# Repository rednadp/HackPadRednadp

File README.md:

# HackPadRednadp
I have tried to create a pad similar to the stremdeck, or at least that was the idea. I have never made something similar and I have found some difficulties along the way. If you want to mount yourself the Pad you will need the materials listed bellow and the 3d-printed case.
# Final build

# Journal 
The desing is not journaled, only the building, sorry :)
# 2/7/2026 - Mounting the pcb day 1  

_Time spent: 2.0h_  

Hello, today I have been trying to figure out how to solder the components to the PCB. After watching some YouTube tutorials, I have "learned" how to solder, but when I tried to put it into practice, I encountered some problems. The first one was figuring out the positions of the components. Once that was solved, I started soldering the LED, but I had some difficulties because the pins were connecting to each other. Finally, I successfully managed to fix that, but with all those problems, I only had time to connect the LED and the diodes. I spent around 2 hours. I will continue another day. Again, sorry for my English it is not my native language :)

# 2/10/2026 10 PM - Mounting the pcb day 2  

_Time spent: 3.0h_  

Hello, today I have finished mounting all the parts to the pcb. I have found some difficulties in aligning the screen with the top plate perfectly as I have to leave a space between them because if not, the screen is too low to be seen with the cover putted.

Another difficulty that I have encountered has been inserting the inserts into the cover. I have never made it and I have made the error of not watching any tutorial, so I have done horribly bad and I will need to reprint the case and try another form of gathering the top and the bottom. The screws don't enter into the hole as it is deformed.

I also realize the necessity of modeling some stuff to turn the potentiometer better.

# 2/10/2026 11 PM - Making Rotary encoder more beautiful  

_Time spent: 0.5h_  

Hello again. I have designed stuff to put in the rotary encoder to make it more beautiful. Sadly for me I have adjusted the tolerances badly and I have to redo it again setting a compensation of -0,4mm. And, again, I have made bad adjustments so I finall decided to modify the design to make it properly.

Design:
.png)

1st attempt:

Other attempts:

# 2/17/2026 - Trying to configure the  firmware  

_Time spent: 4.0h_  

Hello, today I have suffered trying to configure the firmware. I have installed KMK into the Xiao and put all the libraries on their site. I have found some difficulties to see the errors (I have tried to use arduino IDE but after a nice talk with Gemini I have given up and I have donwloaded a program called Mu editor). I have copied the code that I did and I have realised the first problem, the pins. They were different from the diagram, (or thats what I think after intensive research on the internet and with Gemini). Finally, I have gotten the pin layout (d1, d2, etc). Then I had changed the pinout only to realise that the last row of keys was not working. Fixing that has been a terrible task. I have spent around 2 whole hours trying to figure out what was happening, if it was the pinout, another thing in the code or the hardware itself. Finally, it has resulted in one solder of the chip. This has cost me a lot of time because I was checking the connections between the keys and the connections of the pins that went to the xiao but not the connections with the pins and the Xiao (which was the real problem).

The diagram that I have make to have clear the pins: (I know, I am an artist)

Then, I have written the code to display things on the oled display. This has cost me another horrible hour of debugging as I had used a wrong library that was called exactly the same :). Then the text in the display was the other way around. Gemini was saying something about rotate and this has only confused me. Finally, checking the cases of the library, I have discovered that it was flip instead of rotate.

Finally, when I wrote the code to use the leds these have not been put on. I have spent another hour trying to figure out that when I was designing the pcb I used a footprint that was intended for underglow the key. 

I am really tired after debugging problems all the afternoon so I will need to desolder all the leds and solder them all the other way around other day as I cannot redesign the pcb. This is an unexpected change so probably I will have to redesign the case to make it more finer the base to let the ligh pass though it.  

# 2/18/2026 - Give up on LEDS  

_Time spent: 1.5h_  

Bad news, I won't be able to make work the leds. Today I have started trying to desolder the first led (what a difficult task). After literally destroying the led and scratching a lot to expose the connections I have been able to solder a new led.

Leds before solding:

Fist led solded and comparison with the destroyed one:

I have made all the continuity checks with the multimeter and checked that it receives 5v. For my desperation, the led was still not working so I started to realise that maybe the only problem was not the position of the led (that the blueprint that I have used is for underlight the key, not for the key itself) but the pins order. Comparing with the docs of the led I started to suspect that even changing the direction of the led the information pins (In and Out) were upside down so it would be impossible making them work without redesigning the pcb (something impossible, unfortunately). To corroborate that theory, I have asked the help of my brother and my dad to connect another led with cables directly (tanks for your help :) and, by the way, discarding code or other types of errors.

Sadly, my theory was confirmed. The layout of the pins in the pcb was incorrect and there was no way of putting them in a way that they would work. I have had to refuse to use them. With all this, I will make the final touches, and I will test everything.  

# 2/19/2026 - Final touches  

_Time spent: 0.5h_  

Hello, this is my last Journal (or thats what I hope so). I have finished the proyect :))) I'm super happy as it has been my first hadware proyect, and also my first proyect in all hackclub. Thanks to all people making this possible.

I have mount the pad again and I have made some changes to the code to show in the screen the current volume.

# 3/4/2026 - Updated Readme  

_Time spent: 0.5h_  

Hello, I have updated the readme to show the final build as it has been especified by the reviewer. I hope this will make able to ship the HackPad finally.

.png)

# Bill of Materials
 - Seeed XIAO RP2040
 - Through-hole 1N4148 Diodes (x9)
 - MX-Style switches (x9)
 - EC11 Rotary encoder
 - 0.91 inch OLED display
 - Blank DSA keycaps
 - SK6812 MINI-E LEDs (x8)
 - M3x16mm screws (x4)
 - M3x5mx4mm heatset inserts (x4)
 - Printed parts
# Photos

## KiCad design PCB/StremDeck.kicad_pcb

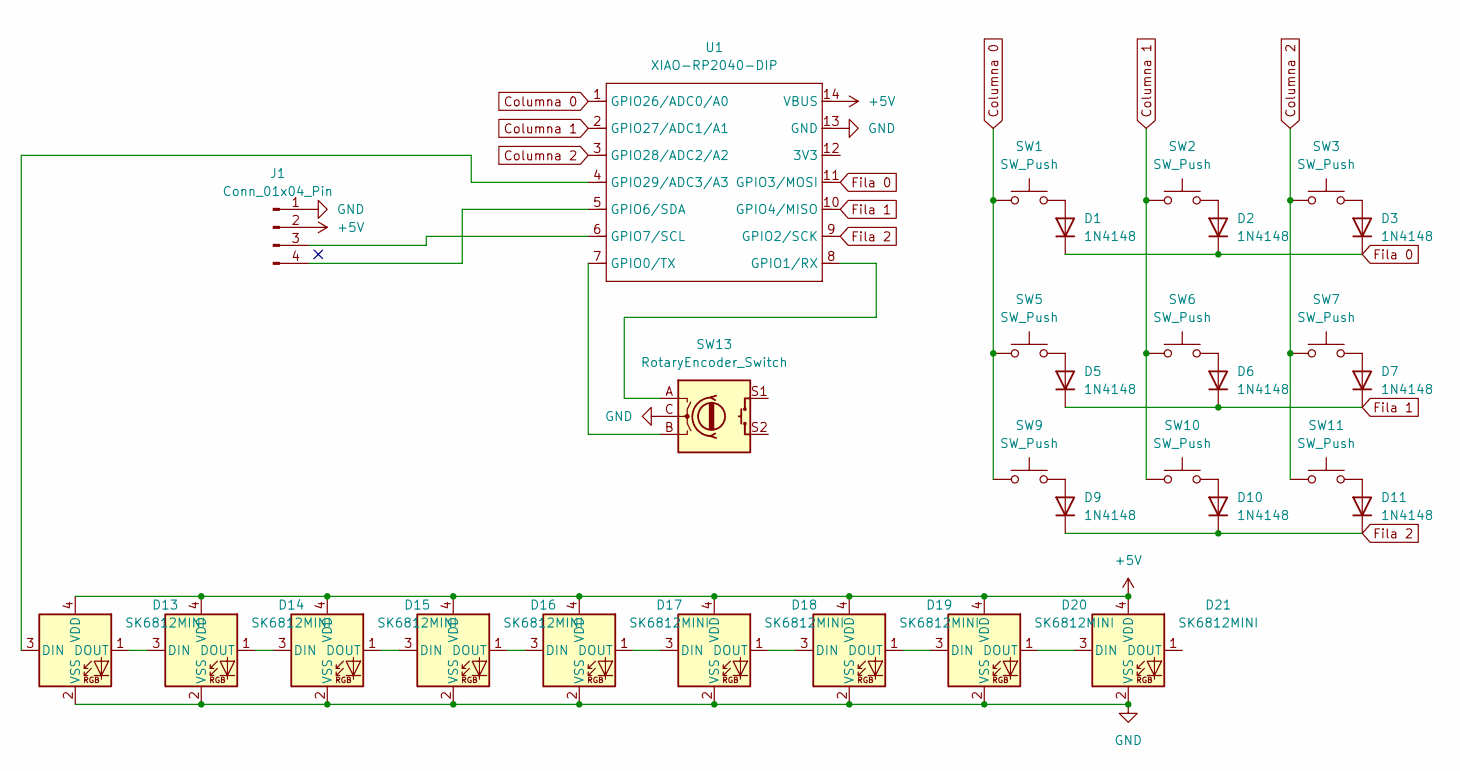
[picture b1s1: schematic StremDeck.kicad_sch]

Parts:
D1, D2, D3, D5, D6, D7, D9, D10, D11: 1N4148; D_DO-35_SOD27_P7.62mm_Horizontal
D13, D14, D15, D16, D17, D18, D19, D20, D21: SK6812MINI; SK6812-MINI-E
J1: Conn_01x04_Pin; SSD1306-0.91-OLED-4pin-128x32
SW1, SW2, SW3, SW5, SW6, SW7, SW9, SW10, SW11: SW_Push; SW_Cherry_MX_1.00u_PCB
SW13: RotaryEncoder_Switch; RotaryEncoder_Alps_EC11E-Switch_Vertical_H20mm
U1: XIAO-RP2040-DIP

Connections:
+5V: D13.4 (VDD), D14.4 (VDD), D15.4 (VDD), D16.4 (VDD), D17.4 (VDD), D18.4 (VDD), D19.4 (VDD), D20.4 (VDD), D21.4 (VDD), J1.2, U1.14 (VBUS)
Columna 0: SW1.1, SW5.1, SW9.1, U1.1 (GPIO26/ADC0/A0)
Columna 1: SW2.1, SW6.1, SW10.1, U1.2 (GPIO27/ADC1/A1)
Columna 2: SW3.1, SW7.1, SW11.1, U1.3 (GPIO28/ADC2/A2)
Fila 0: D1.1 (K), D2.1 (K), D3.1 (K), U1.11 (GPIO3/MOSI)
Fila 1: D5.1 (K), D6.1 (K), D7.1 (K), U1.10 (GPIO4/MISO)
Fila 2: D9.1 (K), D10.1 (K), D11.1 (K), U1.9 (GPIO2/SCK)
GND: D13.2 (VSS), D14.2 (VSS), D15.2 (VSS), D16.2 (VSS), D17.2 (VSS), D18.2 (VSS), D19.2 (VSS), D20.2 (VSS), D21.2 (VSS), J1.1, SW13.C, U1.13 (GND)
unnamed: D1.2 (A), SW1.2
unnamed: D2.2 (A), SW2.2
unnamed: D3.2 (A), SW3.2
unnamed: D5.2 (A), SW5.2
unnamed: D6.2 (A), SW6.2
unnamed: D7.2 (A), SW7.2
unnamed: D9.2 (A), SW9.2
unnamed: D10.2 (A), SW10.2
unnamed: D11.2 (A), SW11.2
unnamed: D13.3 (DIN), U1.4 (GPIO29/ADC3/A3)
unnamed: D13.1 (DOUT), D14.3 (DIN)
unnamed: D14.1 (DOUT), D15.3 (DIN)
unnamed: D15.1 (DOUT), D16.3 (DIN)
unnamed: D16.1 (DOUT), D17.3 (DIN)
unnamed: D17.1 (DOUT), D18.3 (DIN)
unnamed: D18.1 (DOUT), D19.3 (DIN)
unnamed: D19.1 (DOUT), D20.3 (DIN)
unnamed: D20.1 (DOUT), D21.3 (DIN)
unnamed: J1.3, U1.6 (GPIO7/SCL)
unnamed: J1.4, U1.5 (GPIO6/SDA)
unnamed: SW13.B, U1.7 (GPIO0/TX)
unnamed: SW13.A, U1.8 (GPIO1/RX)

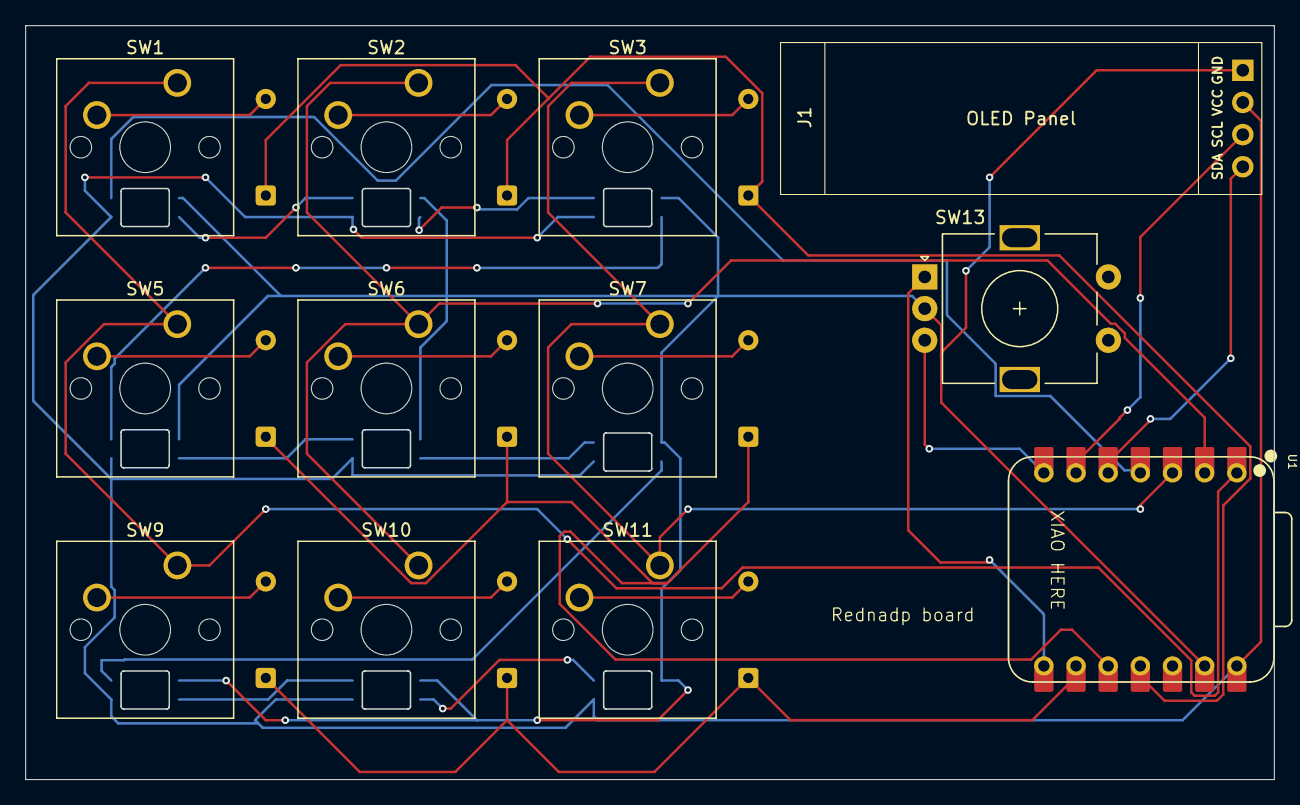
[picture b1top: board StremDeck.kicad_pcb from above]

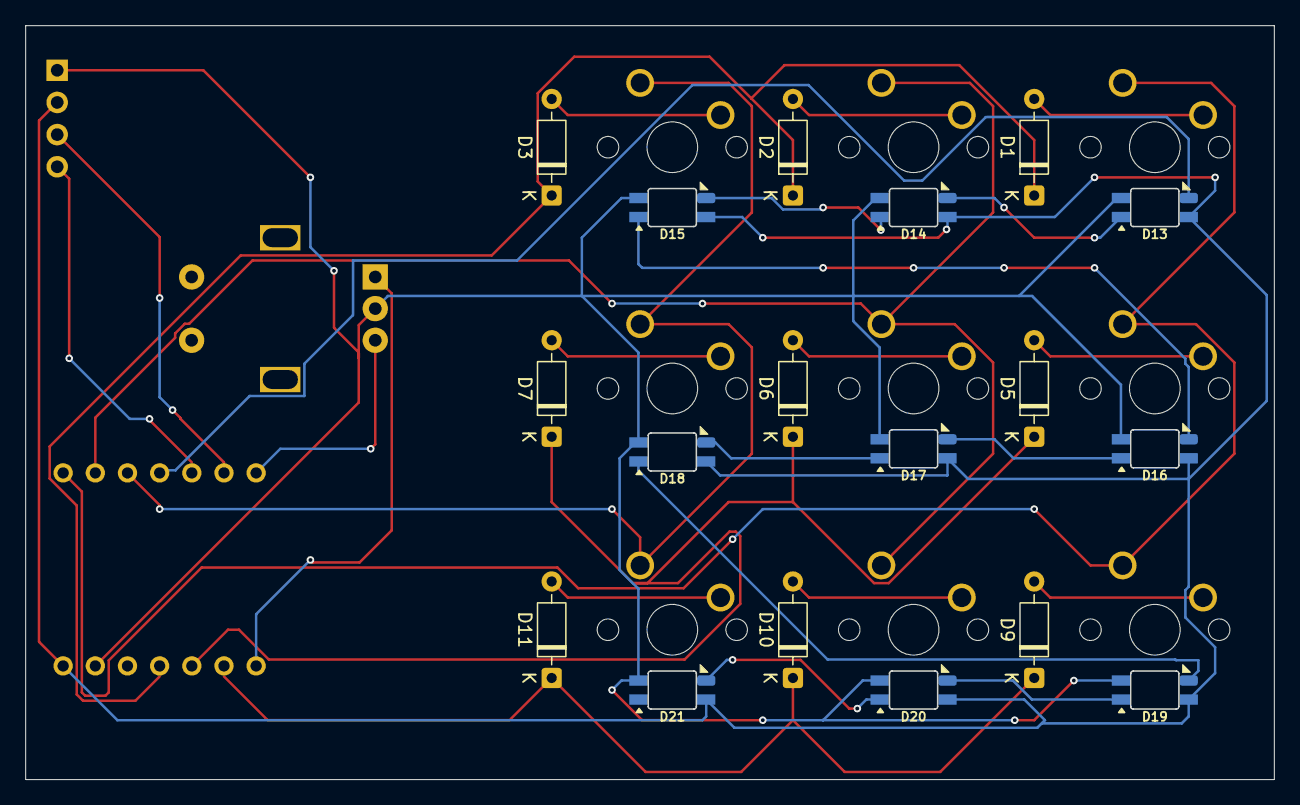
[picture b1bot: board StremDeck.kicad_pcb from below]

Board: 2 copper layers, 98.5 x 59.5 mm, 30 parts (18 on the bottom side), 30 nets.

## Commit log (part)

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2025-12-29 Enhance README with images and BOM
    Added images and a bill of materials section to README.
2025-12-29 Format Bill of Materials list with bullet points
2025-12-29 Restore Photos section in README
    Readded photo section with images to README.
2026-02-10 Rotary ecncoder desing uploaded
2026-02-17 Changed the name to be recongnized by the fimware and modified the code
2026-02-19 Code updated to saw the volume value
2026-03-04 Updated readme to add the finall build
    Expanded project description and added build image.
2026-03-04 Fix typo in 'Final build' section header
